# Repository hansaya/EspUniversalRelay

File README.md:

# EspUniversalRelay
Universal Relay board with esp32

Features
* 3 isolated Relay outputs
* 3 non isolated inputs
* 1 isolated input
* Wide input voltage range
* Super capacitor to harvest energy from a garage door switch.
* Carbon and temperature sensor

#TODO
* Add a 5v and 3v out pins
* Add GND pins for the inputs

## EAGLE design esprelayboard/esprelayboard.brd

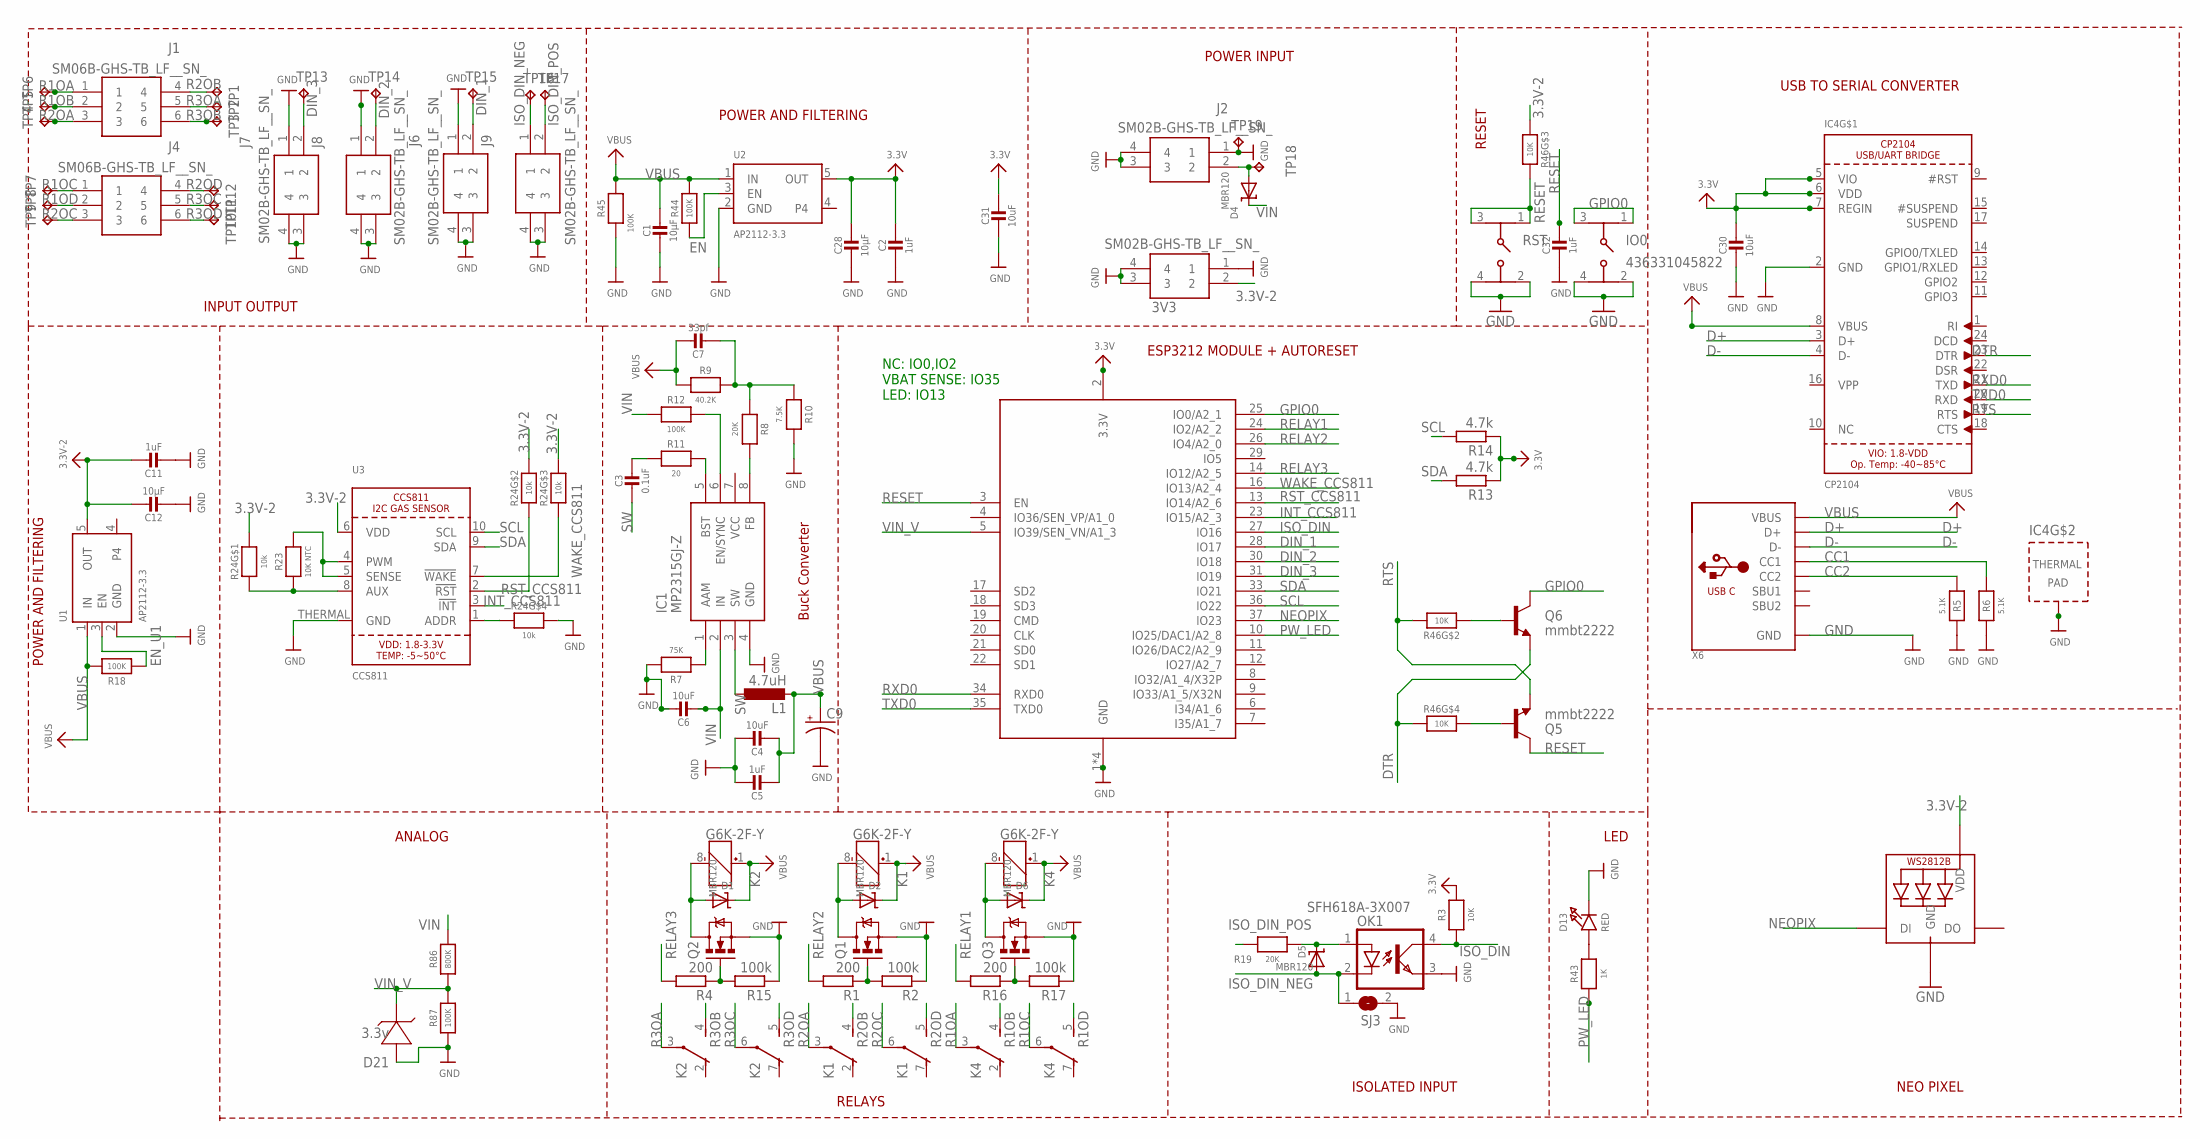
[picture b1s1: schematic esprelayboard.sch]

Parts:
3V3: SM02B-GHS-TB_LF__SN_; SM02BGHSTBLFSN
C1, C12, C28: 10µF; 0805-NO
C2, C5, C11, C32: 1uF; 0603-NO@1
C3: 0.1uF; 0603-NO@1
C4, C6: 10uF; 0603-NO@1
C7: 33pf; 0603-NO@1
C9: CPOL-USUD-6,3X5,8; UD-6,3X5,8_NICHICON
C30, C31: 10uF; 0805-NO
D1, D2, D4, D5, D6: MBR120; SOD-123
D13: RED; CHIPLED_0805_NOOUTLINE
D21: 3.3v; SOD123
IC1: MP2315GJ-Z; SOT65P280X100-8N
IC4: CP2104; QFN24_4MM_SMSC
IO0: 436331045822
J1, J4: SM06B-GHS-TB_LF__SN_; SM06B-GHS-TB
J2, J6, J7, J8, J9: SM02B-GHS-TB_LF__SN_; SM02BGHSTBLFSN
K1, K2, K4: G6K-2F-Y
L1: 4.7uH; L2825P
LED1: WS2812B3535; LED3535
OK1: SFH618A-3X007; SMD4-7
Q1, Q2, Q3: MOSFET-NCHANNELAO3404A; SOT23-3
Q5, Q6: mmbt2222; SOT23-3
R1, R4, R16: 200; R0603
R2, R15, R17: 100k; R0603
R3: 10K; 0603-NO
R5, R6: 5.1K; 0603-NO
R7: 75K; 0603-NO
R8, R19: 20K; 0603-NO
R9: 40.2K; 0603-NO
R10: 7.5K; 0603-NO
R11: 20; 0603-NO
R12, R18, R44, R45, R87: 100K; 0603-NO
R13, R14: 4.7k; R0603
R23: 10K NTC; _0402
R24: 10k; RESPACK_4X0603
R43: 1K; 0603-NO
R46: 10K; RESPACK_4X0603
R86: 800K; 0603-NO
RST: 436331045822
SJ3: SJ
TP1, TP2, TP3, TP4, TP5, TP6, TP7, TP8, TP9, TP10, TP11, TP12, TP13, TP14, TP15, TP16, TP17, TP18, TP19: TPTP14SQ; TP14SQ
U1, U2: AP2112-3.3; SOT23-5
U3: CCS811
X6: USB_C; USB_C_CUSB31-CFM2AX-01-X
X8: ESP32_WROOM32_SKINNY; WROOM32_SKINNY

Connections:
3.3V: C2.1, C28.1, C31.1, R3.1, R13.1, R14.1, U2.5 (OUT), X8.2 (3.3V)
3.3V-2: 3V3.2, C11.1, C12.1, C30.1, IC4.5 (VIO), IC4.6 (VDD), IC4.7 (REGIN), LED1.2 (VDD), R24.6 (2), R24.7 (2), R24.8 (2), R46.3 (1), U1.5 (OUT), U3.6 (VDD)
CC1: R6.2, X6.A5 (CC1)
CC2: R5.2, X6.B5 (CC2)
D+: IC4.3 (D+), X6.A6 (D+), X6.B6 (D+)
D-: IC4.4 (D-), X6.A7 (D-), X6.B7 (D-)
DIN_1: J6.2, TP15.TP, X8.28 (IO17)
DIN_2: J8.2, TP14.TP, X8.30 (IO18)
DIN_3: J7.2, TP13.TP, X8.31 (IO19)
DTR: IC4.23 (DTR), Q6.2 (E), R46.4 (1)
EN: R44.1, U2.3 (EN)
EN_U1: R18.1, U1.3 (EN)
GND: 3V3.1, 3V3.3, 3V3.4, C1.2, C2.2, C4.1, C5.1, C6.1, C9.-, C11.2, C12.2, C28.2, C30.2, C31.2, C32.2, D13.C, D21.A (+), IC1.4 (GND), IC4.2 (GND), IC4.THERM (TP), IO0.2 (4), IO0.4 (2), J2.1, J2.3, J2.4, J6.1, J6.3, J6.4, J7.1, J7.3, J7.4, J8.1, J8.3, J8.4, J9.3, J9.4, LED1.4 (GND), OK1.3 (EMIT), Q1.2 (S), Q2.2 (S), Q3.2 (S), R2.1, R5.1, R6.1, R7.2, R10.2, R15.1, R17.1, R24.5 (2), R45.1, R87.1, RST.2 (4), RST.4 (2), SJ3.2, TP19.TP, U1.2 (GND), U2.2 (GND), U3.THERMAL (GND), X6.A1B12 (GND), X6.B1A12 (GND), X8.1 (GND), X8.15 (GND), X8.38 (GND), X8.P$1 (GND)
GPIO0: IO0.1 (3), IO0.3 (1), Q6.3 (C), X8.25 (IO0/A2_1)
INT_CCS811: U3.3 (!INT), X8.23 (IO15/A2_3)
ISO_DIN: OK1.4 (COL), R3.2, X8.27 (IO16)
ISO_DIN_NEG: D5.A, J9.1, OK1.2 (C), SJ3.1, TP16.TP
ISO_DIN_POS: J9.2, R19.2, TP17.TP
unnamed: D13.A, R43.2
unnamed: Q1.1 (G), R1.1, R2.2
unnamed: D2.A, K1.8 (-), Q1.3 (D)
unnamed: D4.A, J2.2, TP18.TP
unnamed: Q2.1 (G), R4.1, R15.2
unnamed: Q3.1 (G), R16.1, R17.2
unnamed: D1.A, K2.8 (-), Q2.3 (D)
unnamed: D6.A, K4.8 (-), Q3.3 (D)
unnamed: D5.C, OK1.1 (A), R19.1
unnamed: R23.2, U3.4 (PWM), U3.5 (SENSE)
unnamed: R23.1, R24.1, U3.8 (AUX)
unnamed: R24.4 (1), U3.1 (ADDR)
unnamed: IC1.8 (FB), R8.2
unnamed: C7.2, R8.1, R9.2, R10.1
unnamed: IC1.5 (BST), R11.2
unnamed: IC1.1 (AAM), R7.1
unnamed: IC1.6 (EN/SYNC), R12.2
unnamed: C3.1, R11.1
unnamed: Q5.1 (B), R46.5 (2)
unnamed: Q6.1 (B), R46.2 (1)
NEOPIX: LED1.1 (DI), X8.37 (IO23)
PW_LED: R43.1, X8.10 (IO25/DAC1/A2_8)
R1OA: J1.1, K4.3, TP6.TP
R1OB: J1.2, K4.4 (S), TP5.TP
R1OC: J4.1, K4.6, TP7.TP
R1OD: J4.2, K4.5 (S), TP8.TP
R2OA: J1.3, K1.3, TP4.TP
R2OB: J1.4, K1.4 (S), TP1.TP
R2OC: J4.3, K1.6, TP9.TP
R2OD: J4.4, K1.5 (S), TP12.TP
R3OA: J1.5, K2.3, TP2.TP
R3OB: J1.6, K2.4 (S), TP3.TP
R3OC: J4.5, K2.6, TP11.TP
R3OD: J4.6, K2.5 (S), TP10.TP
RELAY1: R16.2, X8.24 (IO2/A2_2)
RELAY2: R1.2, X8.26 (IO4/A2_0)
RELAY3: R4.2, X8.14 (IO12/A2_5)
RESET: C32.1, Q5.3 (C), R46.6 (2), RST.1 (3), RST.3 (1), X8.3 (EN)
RST_CCS811: R24.2 (1), U3.2 (!RST), X8.13 (IO14/A2_6)
RTS: IC4.19 (RTS), Q5.2 (E), R46.7 (2)
RXD0: IC4.21 (TXD), X8.34 (RXD0)
SCL: R14.2, U3.10 (SCL), X8.36 (IO22)
SDA: R13.2, U3.9 (SDA), X8.33 (IO21)
SW: C3.2, IC1.3 (SW), L1.1
TXD0: IC4.20 (RXD), X8.35 (TXD0)
VBUS: C1.1, C4.2, C5.2, C7.1, C9.+, D1.C, D2.C, D6.C, IC4.8 (VBUS), K1.1 (+), K2.1 (+), K4.1 (+), L1.2, R9.1, R18.2, R44.2, R45.2, U1.1 (IN), U2.1 (IN), X6.A4B9 (VBUS), X6.B4A9 (VBUS)
VIN: C6.2, D4.C, IC1.2 (IN), R12.1, R86.2
VIN_V: D21.C (-), R86.1, R87.2, X8.5 (IO39/SEN_VN/A1_3)
WAKE_CCS811: R24.3 (1), U3.7 (!WAKE), X8.16 (IO13/A2_4)

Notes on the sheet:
RESET
LED
ESP3212 MODULE + AUTORESET
NC: IO0,IO2 VBAT SENSE: IO35 LED: IO13
USB TO SERIAL CONVERTER
POWER AND FILTERING
Buck Converter
INPUT OUTPUT
ANALOG
RELAYS
ISOLATED INPUT
NEO PIXEL
POWER INPUT

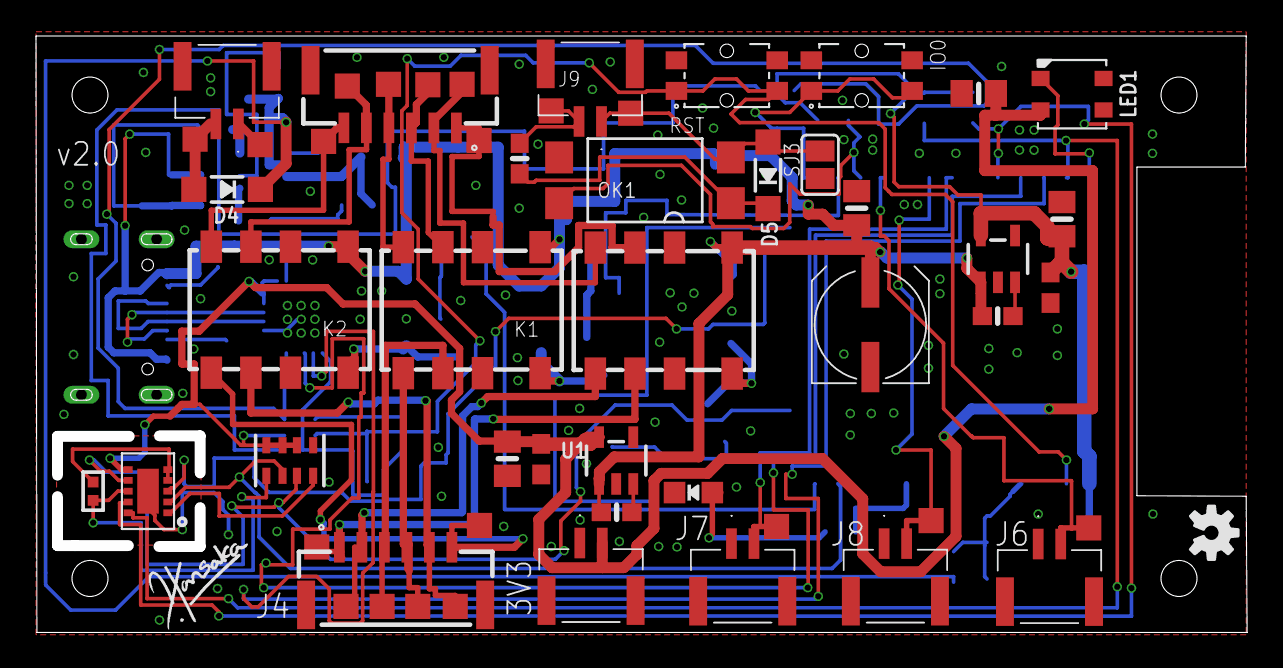
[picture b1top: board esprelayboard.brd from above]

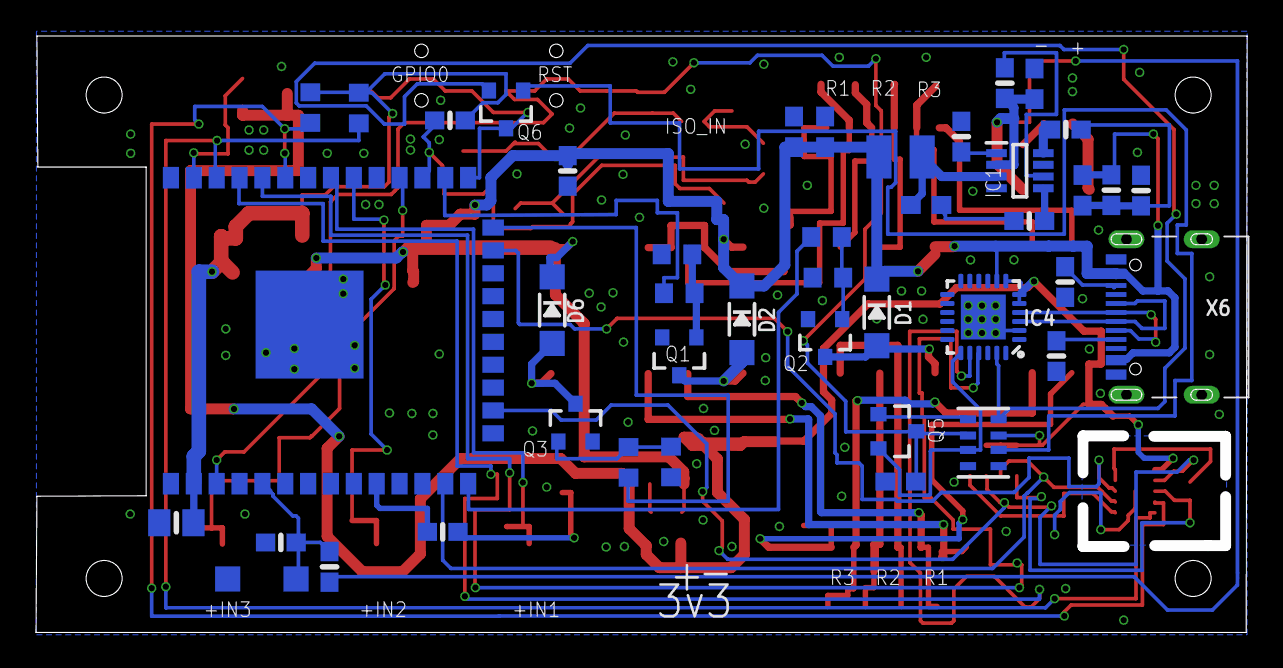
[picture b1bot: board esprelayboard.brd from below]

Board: 2 copper layers, 66.7 x 32.5 mm, 98 parts (43 on the bottom side), 67 nets.

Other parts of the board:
U$38: SIGNATURE
U$39: OSHW-LOGO-S

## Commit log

2020-06-22 v1 layout
2020-07-01 final board files
2020-07-22 doc updates
2020-07-24 bug fix
2020-08-09 updated cam

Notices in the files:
parts and their libraries:
SparkFun-DiscreteSemi: Licensing: CC v3.0 Share-Alike You are welcome to use this library for commercial purposes.
SparkFun-Aesthetics: Licensing: Creative Commons ShareAlike 4.0 International - https://creativecommons.org/licenses/by-sa/4.0
